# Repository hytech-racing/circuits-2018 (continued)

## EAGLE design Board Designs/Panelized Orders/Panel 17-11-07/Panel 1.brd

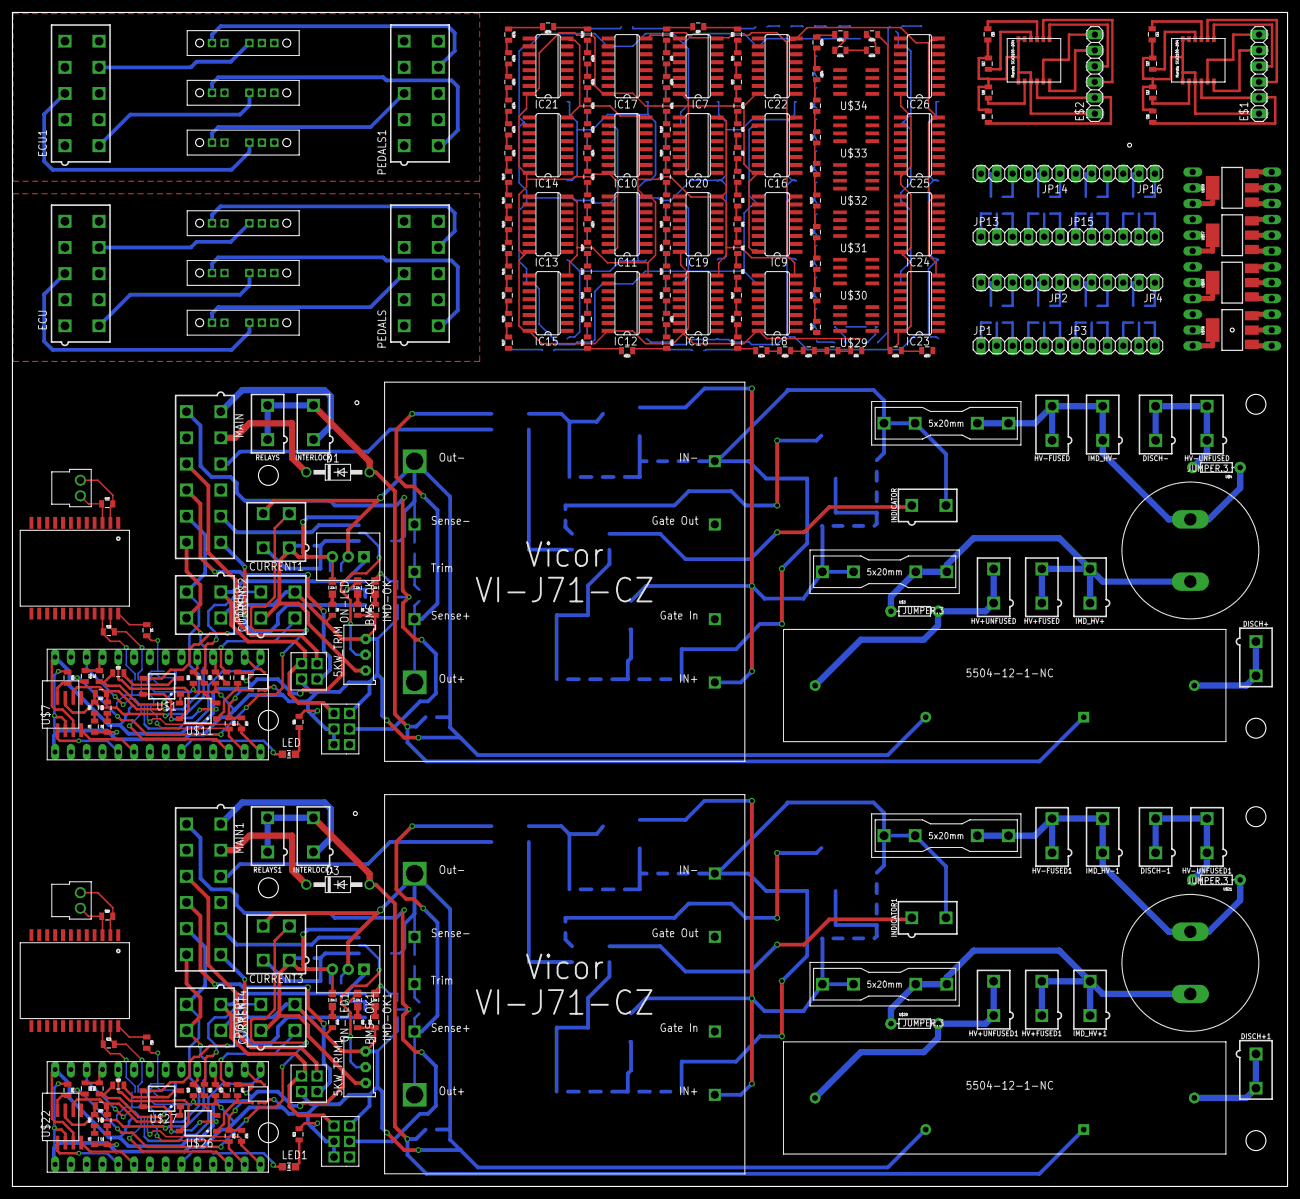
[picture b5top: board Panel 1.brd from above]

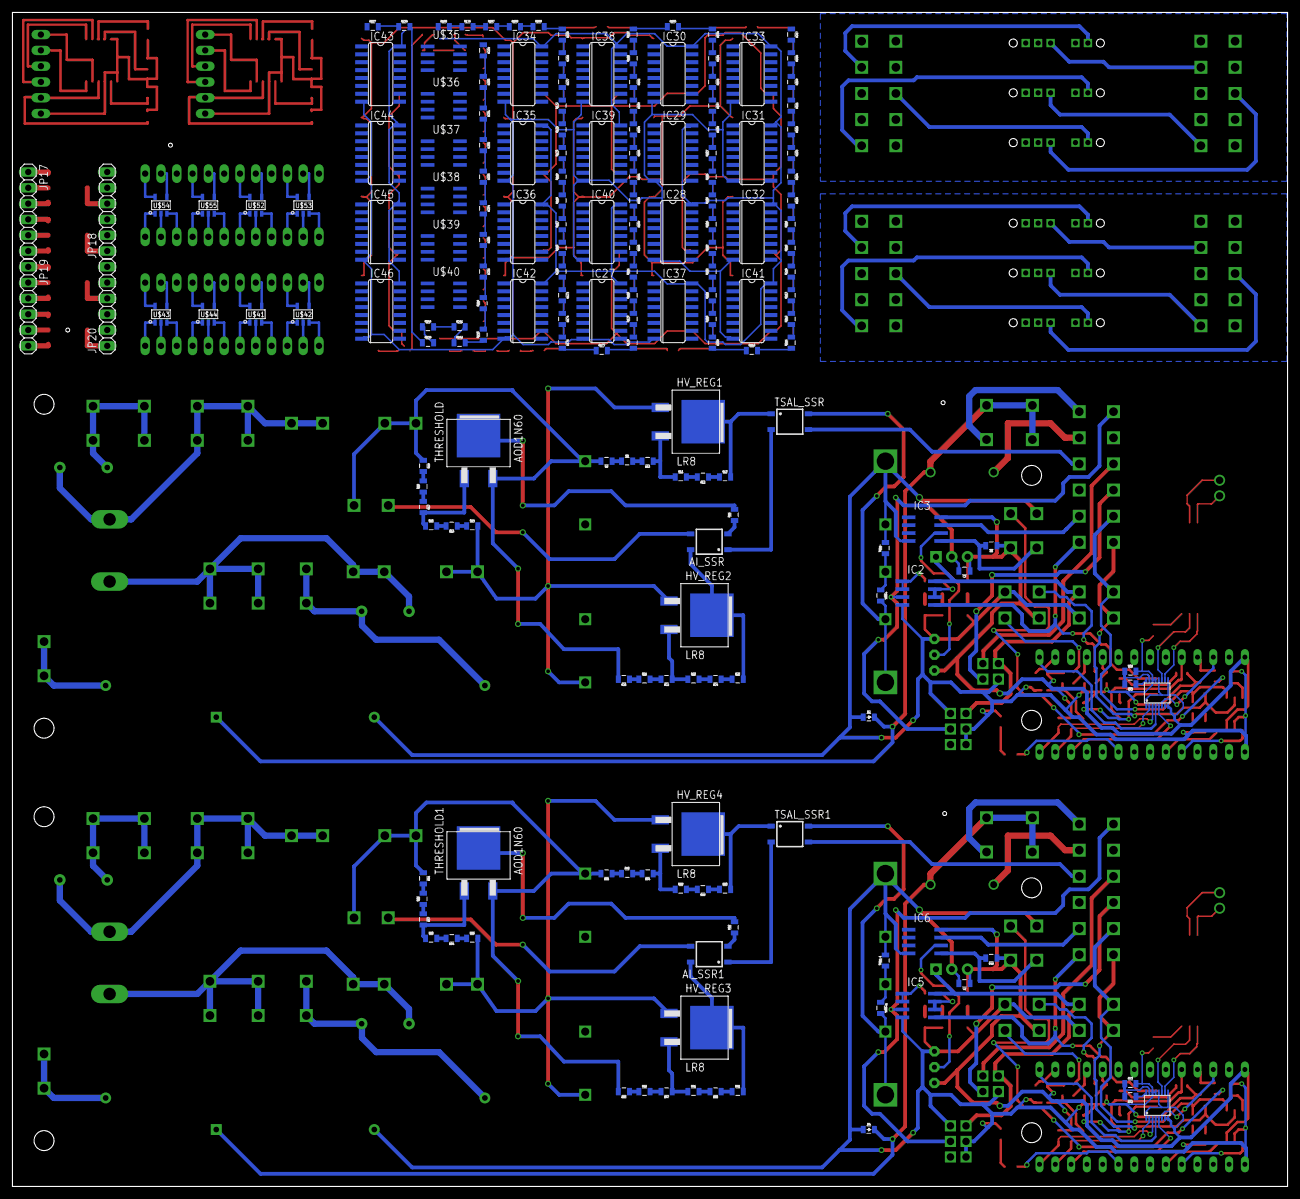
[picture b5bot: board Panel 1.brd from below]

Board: 2 copper layers, 205.0 x 188.7 mm, 448 parts (186 on the bottom side), 404 nets.

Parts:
5KW_TRIM, 5KW_TRIM1: TRIMPOT_3296
AI_SSR, AI_SSR1: CPC1002N; SOP04
BMS-OK, BMS-OK1: LED-805
C1, C5: 220uF; LLS2V221MELZ
C2, C3: 1uF; 0805
C4, C10: 27pF; 0805
C6, C7, C8, C9: 560pF; 0805
C11, C12, C13, C14, C15, C16, C17, C18: 130 nF; 0805
CURRENT1, CURRENT2, CURRENT3, CURRENT4: MINIFIT_5566-4
D1, D3: DIODE; DO-41
D2, D4: DIODE0805; 0805_D
DISCH+, DISCH+1: DISCHARGE+; MINIFIT_5566-2
DISCH-, DISCH-1: DISCHARGE -; MINIFIT_5566-2
E$1, E$2: 1X06
ECU, ECU1: MINIFIT_5566-10
EM, EM1: CONNECTOR-4; NANO-FIT_VERTICAL-4
FUSE, FUSE1, FUSE2, FUSE3: 1A; 0751.0110
HV+FUSED, HV+FUSED1: MINIFIT_5566-2
HV+UNFUSED, HV+UNFUSED1: FSAE; MINIFIT_5566-2
HV-FUSED, HV-FUSED1: MINIFIT_5566-2
HV-UNFUSED, HV-UNFUSED1: FSAE; MINIFIT_5566-2
HV_REG1, HV_REG2, HV_REG3, HV_REG4: LR8; TO-252
IC1, IC4: TO-220
IC2, IC3, IC5, IC6: NE5532SOIC; SOIC-08
IC7, IC8, IC9, IC10, IC11, IC12, IC13, IC14, IC15, IC16, IC17, IC18, IC19, IC20, IC21, IC22, IC23, IC24, IC25, IC26, IC27, IC28, IC29, IC30, IC31, IC32, IC33, IC34, IC35, IC36, IC37, IC38, IC39, IC40, IC41, IC42, IC43, IC44, IC45, IC46: 74LS258D; SO16
IMD, IMD1: CONNECTOR-6; NANO-FIT_VERTICAL-6
IMD-OK, IMD-OK1: LED-805
IMD_HV+, IMD_HV+1: MINIFIT_5566-2
IMD_HV-, IMD_HV-1: MINIFIT_5566-2
INDICATOR, INDICATOR1: MINIFIT_5566-2
INTERLOCK, INTERLOCK1: MINIFIT_5566-2
ISOSPI, ISOSPI1: CONNECTOR-2; NANO-FIT_VERTICAL-2
JP1, JP2, JP3, JP4, JP13, JP14, JP15, JP16, JP17, JP18, JP19, JP20: 1X06
LED, LED1: LED-805
MAIN, MAIN1: MINIFIT_5566-12
ON-LED, ON-LED1: LED-805
PEDALS, PEDALS1: MINIFIT_5566-10
POWER, POWER1: MINIFIT_5566-4
R1, R2, R26, R30, R33, R34, R44, R52, R70, R72, R73, R78, R79, R82: 1k; 0805
R3, R4, R31, R45, R46, R71, R85, R86, R87, R88, R89, R90, R91, R92, R93, R94, R95, R96, R97, R98, R99, R100, R101, R102, R103, R104, R105, R106, R107, R108, R109, R110, R111, R112, R113, R114, R115, R116, R117, R118, R119, R120, R121, R122, R123, R124, R125, R126, R127, R128, R129, R130, R131, R132, R133, R134, R135, R136, R137, R138, R139, R140, R141, R142, R143, R144, R145, R146, R147, R148, R149, R150, R151, R152, R153, R154, R155, R156, R157, R158, R159, R160, R161, R162, R163, R164, R165, R166, R167, R168, R169, R170, R171, R172, R173, R174, R175, R176, R177, R178, R179, R180, R181, R182, R183, R184, R185, R186, R187, R188, R189, R190, R191, R192, R193, R194, R195, R196, R197, R198, R199, R200, R201, R202, R203, R204, R205, R206, R207, R208, R209, R210, R211, R212, R213, R214, R215, R216, R217, R218, R219, R220, R221, R222, R223, R224, R225, R226, R227, R228, R229, R230, R231, R232, R233, R234, R235, R236, R237, R238, R239, R240, R241, R242, R243, R244: 0805
R5, R28, R29, R40, R49, R68, R69, R84: 100; 0805
R6, R48: 10k; 0805
R7, R11, R12, R13, R23, R24, R25, R32, R36, R37, R41, R42, R43, R53, R58, R59, R60, R61, R75, R76, R80, R81: 2k; 0805
R8, R9, R10, R64, R65, R66: 8.2k; 0805
R14, R15, R16, R50, R54, R55: 500k; 0805
R17, R18, R19, R51, R56, R57: 40k; 0805
R20, R21, R22, R47, R62, R63: 20k; 0805
R27, R35, R67, R74: 120; 0805
R38, R77: 68; 0805
R39, R83: 200; 0805
RELAYS, RELAYS1: MINIFIT_5566-2
THRESHOLD, THRESHOLD1: AOD1N60; TO-252
TRIM+, TRIM+1: 0805
TRIM-, TRIM-1: 0805
TSAL_SSR, TSAL_SSR1: CPC1002N; SOP04
U$1, U$11, U$26, U$27: SOP04
U$2, U$28: SM51589PEL
U$3, U$4, U$20, U$21: JUMPER.3; AXIAL-0.3
U$5, U$19: HV_DCDC_VI-J71-CZ
U$6, U$13, U$14, U$15, U$16, U$17: SS-14D0839-VG5PA
U$7, U$22, U$29, U$30, U$31, U$32, U$33, U$34, U$35, U$36, U$37, U$38, U$39, U$40: MCP2551; SOIC-08
U$8, U$23: LTC6820; MSOP-16
U$9, U$24: TEENSY_3.2_SIMPLE
U$10, U$25: STWD100; SOT23-5
U$12, U$18: 5504-12-1-NC
U$41, U$43, U$52, U$54: SN74LVC1G06; SOT-23-5
U$42, U$44, U$53, U$55: SN74LVC1G07; SOT-23-5
U$45, U$56: SCA3100-D04
U$57, U$58, U$59, U$60: SOT223

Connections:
5KW_TRIG: 5KW_TRIM.2, IC3.6
5KW_TRIG1: 5KW_TRIM1.2, IC6.6
+3V1: U$23.6, U$24.3.3V
+3V3: U$8.6, U$9.3.3V
+5V: 5KW_TRIM.1, C3.1, CURRENT1.1, CURRENT2.1, IC1.3, IC3.8, ON-LED.A, R6.1, R36.1, R37.1, R38.1, U$1.4, U$7.3, U$8.1, U$8.7, U$8.8, U$8.9, U$8.12, U$9.VIN, U$10.VCC
+5V1: ECU.1, ECU.4, ECU.7, PEDALS.1, PEDALS.4, PEDALS.7, U$6.4, U$13.4, U$14.4
+5V3: 5KW_TRIM1.1, C2.1, CURRENT3.1, CURRENT4.1, IC4.3, IC6.8, ON-LED1.A, R48.1, R75.1, R76.1, R77.1, U$22.3, U$23.1, U$23.7, U$23.8, U$23.9, U$23.12, U$24.VIN, U$25.VCC, U$27.4
+5V4: ECU1.1, ECU1.4, ECU1.7, PEDALS1.1, PEDALS1.4, PEDALS1.7, U$15.4, U$16.4, U$17.4
+12V: EM.P$1, IC1.1, IC2.8, IMD.P$1, POWER.1
+12V1: EM1.P$1, IC4.1, IC5.8, IMD1.P$1, POWER1.1
BMS_OK: IC2.5, MAIN.6, U$1.3
BMS_OK1: IC5.5, MAIN1.6, U$27.3
BMS_WATCH: U$1.1, U$11.3
BMS_WATCH1: U$26.3, U$27.1
BSPD_CUR_FAULT: IC3.7, MAIN.5
BSPD_CUR_FAULT1: IC6.7, MAIN1.5
CANH: MAIN.12, POWER.4, R27.2, R28.2, U$7.7
CANH1: MAIN1.12, POWER1.4, R67.2, R68.2, U$22.7
CANL: MAIN.11, POWER.3, R27.1, R29.2, U$7.6
CANL1: MAIN1.11, POWER1.3, R67.1, R69.2, U$22.6
CS: U$8.5, U$9.D10(TX2)
CS1: U$23.5, U$24.D10(TX2)
CUR_SENSE_1: CURRENT1.2, IC3.5, R6.2
CUR_SENSE_2: R1.1, R32.2, U$9.A3
CUR_SENSE_3: CURRENT3.2, IC6.5, R48.2
CUR_SENSE_4: R78.1, R80.2, U$24.A3
DISCHARGE1: HV+UNFUSED.1, HV+UNFUSED.2, U$3.P$2, U$12.CONTACT1
DISCHARGE2: DISCH+.1, DISCH+.2, U$12.CONTACT2
DISCHARGE3: DISCH-.1, DISCH-.2, HV-UNFUSED.1, HV-UNFUSED.2, U$4.P$2
DISCHARGE4: DISCH+1.1, DISCH+1.2, U$18.CONTACT2
DISCHARGE5: HV+UNFUSED1.1, HV+UNFUSED1.2, U$18.CONTACT1, U$20.P$2
DISCHARGE6: DISCH-1.1, DISCH-1.2, HV-UNFUSED1.1, HV-UNFUSED1.2, U$21.P$2
EM_IO1: EM.P$3, MAIN.9
EM_IO2: EM.P$4, MAIN.10
EM_IO3: EM1.P$3, MAIN1.9
EM_IO4: EM1.P$4, MAIN1.10
GND: 5KW_TRIM.3, C3.2, C4.2, C8.1, C9.1, CURRENT1.4, CURRENT2.4, D2.A, EM.P$2, IC1.2, IC2.4, IC3.4, IMD.P$2, IMD.P$3, IMD.P$4, POWER.2, R3.1, R4.2, R5.2, R7.1, R30.1, R31.2, R32.1, R34.2, R39.1, R43.1, TRIM-.2, U$5.8SENSE-, U$5.9VOUT-, U$7.2, U$8.13, U$8.14, U$9.GND, U$10.EN, U$10.GND, U$11.2, U$12.COIL-
GND1: ECU.2, ECU.5, ECU.8, PEDALS.2, PEDALS.5, PEDALS.8, U$6.3, U$13.3, U$14.3
GND2: ECU1.2, ECU1.5, ECU1.8, PEDALS1.2, PEDALS1.5, PEDALS1.8, U$15.3, U$16.3, U$17.3
GND3: 5KW_TRIM1.3, C2.2, C6.1, C7.1, C10.2, CURRENT3.4, CURRENT4.4, D4.A, EM1.P$2, IC4.2, IC5.4, IC6.4, IMD1.P$2, IMD1.P$3, IMD1.P$4, POWER1.2, R42.1, R45.1, R46.2, R49.2, R70.1, R71.2, R73.2, R80.1, R81.1, R83.1, TRIM-1.2, U$18.COIL-, U$19.8SENSE-, U$19.9VOUT-, U$22.2, U$23.13, U$23.14, U$24.GND, U$25.EN, U$25.GND, U$26.2
GND4: IC7.8, IC8.8, IC9.8, IC10.8, IC11.8, IC12.8, IC13.8, IC14.8, IC15.8, IC16.8, IC17.8, IC18.8, IC19.8, IC20.8, IC21.8, IC22.8, IC23.8, IC24.8, IC25.8, IC26.8
GND5: IC27.8, IC28.8, IC29.8, IC30.8, IC31.8, IC32.8, IC33.8, IC34.8, IC35.8, IC36.8, IC37.8, IC38.8, IC39.8, IC40.8, IC41.8, IC42.8, IC43.8, IC44.8, IC45.8, IC46.8
GND6: C11.2, C12.2, C13.2, C14.2, U$45.AVSS, U$45.DVSS, U$45.EMC_GND, U$45.RESERVED
GND7: C15.2, C16.2, C17.2, C18.2, U$56.AVSS, U$56.DVSS, U$56.EMC_GND, U$56.RESERVED
HV+FUSED: C1.P$1, FUSE.L1, FUSE.L2, HV+FUSED.1, HV+FUSED.2, IMD_HV+.1, IMD_HV+.2, U$3.P$1
HV+FUSED1: C5.P$1, FUSE2.L1, FUSE2.L2, HV+FUSED1.1, HV+FUSED1.2, IMD_HV+1.1, IMD_HV+1.2, U$20.P$1
HV+FUSED_1A: FUSE.R1, FUSE.R2, HV_REG1.1, HV_REG2.1, R14.2, U$5.1VIN+
HV+FUSED_1A1: FUSE2.R1, FUSE2.R2, HV_REG3.1, HV_REG4.1, R55.2, U$19.1VIN+
HV-FUSED: C1.P$2, FUSE1.L1, FUSE1.L2, HV-FUSED.1, HV-FUSED.2, IMD_HV-.1, IMD_HV-.2, U$4.P$1
HV-FUSED1: C5.P$2, FUSE3.L1, FUSE3.L2, HV-FUSED1.1, HV-FUSED1.2, IMD_HV-1.1, IMD_HV-1.2, U$21.P$1
HV-FUSED_1A: FUSE1.R1, FUSE1.R2, INDICATOR.2, R8.2, R19.1, R20.2, THRESHOLD.3, U$5.4VIN-
HV-FUSED_1A1: FUSE3.R1, FUSE3.R2, INDICATOR1.2, R51.1, R63.2, R66.2, THRESHOLD1.3, U$19.4VIN-
ISOSPI-M: ISOSPI.P$2, R40.1, U$2.3
ISOSPI-M1: ISOSPI1.P$2, R84.1, U$28.3
ISOSPI-P: ISOSPI.P$1, R40.2, U$2.2
ISOSPI-P1: ISOSPI1.P$1, R84.2, U$28.2
MISO: R37.2, U$8.3, U$9.D12
MISO1: R76.2, U$23.3, U$24.D12
MOSI: R36.2, U$8.2, U$9.D11
MOSI1: R75.2, U$23.2, U$24.D11
unnamed: AI_SSR.4, HV_REG2.2(TAB), R25.2
unnamed: HV_REG1.2(TAB), R13.2, TSAL_SSR.1
unnamed: ON-LED.C, R5.1
unnamed: R39.2, U$1.2
unnamed: AI_SSR.2, R26.1
unnamed: AI_SSR.1, TSAL_SSR.2
unnamed: AI_SSR.3, INDICATOR.1
unnamed: R8.1, R9.1
unnamed: R26.2, THRESHOLD.2(TAB)
unnamed: R14.1, R15.1
unnamed: R15.2, R16.2
unnamed: R17.1, R18.1
unnamed: R18.2, R19.2
unnamed: R9.2, R10.2
unnamed: HV_REG2.3, R22.1, R23.1
unnamed: R11.2, R12.2
unnamed: R12.1, R13.1
unnamed: HV_REG1.3, R10.1, R11.1
unnamed: R23.2, R24.2
unnamed: R24.1, R25.1
unnamed: R21.2, R22.2
unnamed: R16.1, R17.2, THRESHOLD.1
unnamed: R20.1, R21.1
unnamed: ECU.9, U$6.COM
unnamed: U$7.1, U$9.D3(CANTX)
unnamed: R30.2, U$7.8
unnamed: C8.2, R28.1
unnamed: C9.2, R29.1
unnamed: LED.C, R31.1
unnamed: CURRENT2.2, R1.2
unnamed: R33.1, U$8.16
unnamed: R33.2, R34.1, U$8.15
unnamed: R35.1, U$2.22, U$8.10
unnamed: R35.2, U$2.23, U$8.11
unnamed: C4.1, U$2.24
unnamed: U$7.4, U$9.D4(CANRX)
unnamed: LED.A, U$9.D7(RX3)
unnamed: R38.2, U$10.WDO, U$11.1
unnamed: ECU.6, U$13.COM
unnamed: U$9.A8, U$11.4
unnamed: ECU.3, U$14.COM
unnamed: IC2.1, IC2.2, IMD-OK.A
unnamed: BMS-OK.A, IC2.6, IC2.7
unnamed: BMS-OK.C, R4.1
unnamed: IMD-OK.C, R3.2
unnamed: PEDALS.9, U$6.1
unnamed: PEDALS.6, U$13.1
unnamed: PEDALS.3, U$14.1
unnamed: ECU1.9, U$15.COM
unnamed: U$9.A0, U$10.WDI
unnamed: ECU1.6, U$16.COM
unnamed: ECU1.3, U$17.COM
unnamed: CURRENT1.3, R44.2
unnamed: CURRENT2.3, R2.2
unnamed: PEDALS1.9, U$15.1
unnamed: PEDALS1.6, U$16.1
unnamed: PEDALS1.3, U$17.1
unnamed: AI_SSR1.4, HV_REG3.2(TAB), R61.2
unnamed: HV_REG3.3, R41.1, R47.1
unnamed: IC5.1, IC5.2, IMD-OK1.A
unnamed: BMS-OK1.A, IC5.6, IC5.7
unnamed: BMS-OK1.C, R46.1
unnamed: IMD-OK1.C, R45.2
unnamed: ON-LED1.C, R49.1
unnamed: HV_REG4.2(TAB), R53.2, TSAL_SSR1.1
unnamed: R54.1, R55.1
unnamed: R50.2, R54.2
unnamed: R56.1, R57.1
unnamed: R51.2, R56.2
unnamed: AI_SSR1.2, R52.1
unnamed: AI_SSR1.1, TSAL_SSR1.2
unnamed: AI_SSR1.3, INDICATOR1.1
unnamed: HV_REG4.3, R59.1, R64.1
unnamed: R64.2, R65.2
unnamed: R65.1, R66.1
unnamed: R50.1, R57.2, THRESHOLD1.1
unnamed: R58.2, R59.2
unnamed: R53.1, R58.1
unnamed: R52.2, THRESHOLD1.2(TAB)
unnamed: R41.2, R60.2
unnamed: R60.1, R61.1
unnamed: R47.2, R62.2
unnamed: R62.1, R63.1
unnamed: U$22.1, U$24.D3(CANTX)
unnamed: R70.2, U$22.8
unnamed: C6.2, R68.1
unnamed: C7.2, R69.1
unnamed: LED1.C, R71.1
unnamed: R72.1, U$23.16
unnamed: R72.2, R73.1, U$23.15
unnamed: R74.1, U$23.10, U$28.22
unnamed: R74.2, U$23.11, U$28.23
unnamed: C10.1, U$28.24
unnamed: U$22.4, U$24.D4(CANRX)
unnamed: LED1.A, U$24.D7(RX3)
unnamed: R77.2, U$25.WDO, U$26.1
unnamed: U$24.A8, U$26.4
unnamed: U$24.A0, U$25.WDI
unnamed: CURRENT4.2, R78.2
unnamed: CURRENT4.3, R79.2
unnamed: CURRENT3.3, R82.2
unnamed: R83.2, U$27.2
unnamed: R85.2, R96.1
unnamed: R96.2, R107.1
unnamed: R107.2, R118.1
unnamed: R129.2, R140.1
unnamed: R140.2, R146.1
unnamed: R146.2, R147.1
unnamed: R118.2, R129.1
unnamed: R86.1, R148.2
unnamed: R86.2, R87.1
unnamed: R87.2, R88.1
unnamed: R89.2, R90.1
unnamed: R90.2, R91.1
unnamed: R91.2, R92.1
unnamed: R88.2, R89.1
unnamed: R92.2, R147.2
unnamed: R93.2, R94.1
unnamed: R94.2, R95.1
unnamed: R95.2, R97.1
unnamed: R98.2, R99.1
unnamed: R99.2, R100.1
unnamed: R100.2, R101.1
unnamed: R97.2, R98.1
unnamed: R102.2, R103.1
unnamed: R103.2, R104.1
unnamed: R104.2, R105.1
unnamed: R106.2, R108.1
unnamed: R108.2, R109.1
unnamed: R109.2, R110.1
unnamed: R105.2, R106.1
unnamed: R101.2, R110.2
unnamed: R93.1, R148.1
unnamed: R111.2, R112.1
unnamed: R112.2, R113.1
unnamed: R113.2, R114.1
unnamed: R115.2, R116.1
unnamed: R116.2, R117.1
unnamed: R117.2, R119.1
unnamed: R114.2, R115.1
unnamed: R120.2, R121.1
unnamed: R121.2, R122.1
unnamed: R122.2, R123.1
unnamed: R124.2, R125.1
unnamed: R125.2, R126.1
unnamed: R126.2, R127.1
unnamed: R123.2, R124.1
unnamed: R119.2, R127.2
unnamed: R128.2, R130.1
unnamed: R130.2, R131.1
unnamed: R131.2, R132.1
unnamed: R133.2, R134.1
unnamed: R134.2, R135.1
unnamed: R135.2, R136.1
unnamed: R132.2, R133.1
unnamed: R137.2, R138.1
unnamed: R138.2, R139.1
unnamed: R139.2, R141.1
unnamed: R142.2, R143.1
unnamed: R143.2, R144.1
unnamed: R144.2, R145.1
unnamed: R141.2, R142.1
unnamed: R136.2, R145.2
unnamed: R120.1, R128.1
unnamed: R102.1, R111.1
unnamed: R149.2, R150.1
unnamed: R150.2, R151.1
unnamed: R151.2, R152.1
unnamed: R153.2, R154.1
unnamed: R154.2, R155.1
unnamed: R155.2, R156.1
unnamed: R152.2, R153.1
unnamed: R157.2, R158.1
unnamed: R158.2, R159.1
unnamed: R159.2, R160.1
unnamed: R161.2, R162.1
unnamed: R162.2, R163.1
unnamed: R163.2, R164.1
unnamed: R160.2, R161.1
unnamed: R156.2, R164.2
unnamed: R165.2, R176.1
unnamed: R176.2, R187.1
unnamed: R187.2, R198.1
unnamed: R209.2, R220.1
unnamed: R220.2, R226.1
unnamed: R226.2, R227.1
unnamed: R198.2, R209.1
unnamed: R166.1, R228.2
unnamed: R166.2, R167.1
unnamed: R167.2, R168.1
unnamed: R169.2, R170.1
unnamed: R170.2, R171.1
unnamed: R171.2, R172.1
unnamed: R168.2, R169.1
unnamed: R172.2, R227.2
unnamed: R173.2, R174.1
unnamed: R174.2, R175.1
unnamed: R175.2, R177.1
unnamed: R178.2, R179.1
unnamed: R179.2, R180.1
unnamed: R180.2, R181.1
unnamed: R177.2, R178.1
unnamed: R182.2, R183.1
unnamed: R183.2, R184.1
unnamed: R184.2, R185.1
unnamed: R186.2, R188.1
unnamed: R188.2, R189.1
unnamed: R189.2, R190.1
unnamed: R185.2, R186.1
unnamed: R181.2, R190.2
unnamed: R173.1, R228.1
unnamed: R191.2, R192.1
unnamed: R192.2, R193.1
unnamed: R193.2, R194.1
unnamed: R195.2, R196.1
unnamed: R196.2, R197.1
unnamed: R197.2, R199.1
unnamed: R194.2, R195.1
unnamed: R200.2, R201.1
unnamed: R201.2, R202.1
unnamed: R202.2, R203.1
unnamed: R204.2, R205.1
unnamed: R205.2, R206.1
unnamed: R206.2, R207.1
unnamed: R203.2, R204.1
unnamed: R199.2, R207.2
unnamed: R208.2, R210.1
unnamed: R210.2, R211.1
unnamed: R211.2, R212.1
unnamed: R213.2, R214.1
unnamed: R214.2, R215.1
unnamed: R215.2, R216.1
unnamed: R212.2, R213.1
unnamed: R217.2, R218.1
unnamed: R218.2, R219.1
unnamed: R219.2, R221.1
unnamed: R222.2, R223.1
unnamed: R223.2, R224.1
unnamed: R224.2, R225.1
unnamed: R221.2, R222.1
unnamed: R216.2, R225.2
unnamed: R200.1, R208.1
unnamed: R182.1, R191.1
unnamed: R229.2, R230.1
unnamed: R230.2, R231.1
unnamed: R231.2, R232.1
unnamed: R233.2, R234.1
unnamed: R234.2, R235.1
unnamed: R235.2, R236.1
unnamed: R232.2, R233.1
unnamed: R237.2, R238.1
unnamed: R238.2, R239.1
unnamed: R239.2, R240.1
unnamed: R241.2, R242.1
unnamed: R242.2, R243.1
unnamed: R243.2, R244.1
unnamed: R240.2, R241.1
unnamed: R236.2, R244.2
unnamed: JP2.1, U$41.5
unnamed: JP2.2, U$41.4
unnamed: JP2.4, U$42.5
unnamed: JP2.5, U$42.4
unnamed: JP1.6, U$41.1
unnamed: JP1.5, U$41.2
unnamed: JP1.4, U$41.3
unnamed: JP1.3, U$42.1
unnamed: JP1.2, U$42.2
unnamed: JP1.1, U$42.3
unnamed: JP4.1, U$43.5
unnamed: JP4.2, U$43.4
unnamed: JP4.4, U$44.5
unnamed: JP4.5, U$44.4
unnamed: JP3.6, U$43.1
unnamed: JP3.5, U$43.2
unnamed: JP3.4, U$43.3
unnamed: JP3.3, U$44.1
unnamed: JP3.2, U$44.2
unnamed: JP3.1, U$44.3
unnamed: C12.1, U$45.A_EXTC
unnamed: C13.1, U$45.D_EXTC
unnamed: C14.1, U$45.DVIO
unnamed: JP14.1, U$52.5
unnamed: JP14.2, U$52.4
unnamed: JP14.4, U$53.5
unnamed: JP14.5, U$53.4
unnamed: JP13.6, U$52.1
unnamed: JP13.5, U$52.2
unnamed: JP13.4, U$52.3
unnamed: JP13.3, U$53.1
unnamed: JP13.2, U$53.2
unnamed: JP13.1, U$53.3
unnamed: JP16.1, U$54.5
unnamed: JP16.2, U$54.4
unnamed: JP16.4, U$55.5
unnamed: JP16.5, U$55.4
unnamed: JP15.6, U$54.1
unnamed: JP15.5, U$54.2
unnamed: JP15.4, U$54.3
unnamed: JP15.3, U$55.1
unnamed: JP15.2, U$55.2
unnamed: JP15.1, U$55.3
unnamed: C16.1, U$56.A_EXTC
unnamed: C17.1, U$56.D_EXTC
unnamed: C18.1, U$56.DVIO
unnamed: JP18.1, U$57.4
unnamed: JP17.6, U$57.1
unnamed: JP17.5, U$57.2
unnamed: JP17.4, U$57.3
unnamed: JP17.3, U$59.1
unnamed: JP17.2, U$59.2
unnamed: JP17.1, U$59.3
unnamed: JP18.4, U$59.4
unnamed: JP20.1, U$58.4
unnamed: JP20.4, U$60.4
unnamed: JP19.6, U$58.1
unnamed: JP19.5, U$58.2
unnamed: JP19.4, U$58.3
unnamed: JP19.3, U$60.1
unnamed: JP19.2, U$60.2
unnamed: JP19.1, U$60.3
OKHS: IC2.3, IMD.P$5, MAIN.7
OKHS1: IC5.3, IMD1.P$5, MAIN1.7
SCK: U$8.4, U$9.D13
SCK1: U$23.4, U$24.D13
SHUTDOWN1: D3.A, D4.C, INTERLOCK1.2, RELAYS1.1, RELAYS1.2, U$18.COIL+
SHUTDOWN2: INTERLOCK1.1, MAIN1.1
SHUTDOWN6: INTERLOCK.1, MAIN.1
SHUTDOWN7: D1.A, D2.C, INTERLOCK.2, RELAYS.1, RELAYS.2, U$12.COIL+
SHUTDOWN7_EXT_OUT: D1.C, MAIN.2
SHUTDOWN7_EXT_OUT1: D3.C, MAIN1.2
TEMP_SENSE_1: R7.2, R44.1, U$9.A9
TEMP_SENSE_2: R2.1, R43.2, U$9.A2
TEMP_SENSE_3: R79.1, R81.2, U$24.A2
TEMP_SENSE_4: R42.2, R82.1, U$24.A9
TRIM: TRIM+.1, TRIM-.1, U$5.7TRIM
TRIM1: TRIM+1.1, TRIM-1.1, U$19.7TRIM
TSAL+: MAIN.3, TSAL_SSR.3
TSAL+1: MAIN1.3, TSAL_SSR1.3
TSAL_1: TRIM+.2, TSAL_SSR.4, U$5.5VOUT+, U$5.6SENSE+
TSAL_2: TRIM+1.2, TSAL_SSR1.4, U$19.5VOUT+, U$19.6SENSE+
VCC: IC7.16, IC8.16, IC9.16, IC10.16, IC11.16, IC12.16, IC13.16, IC14.16, IC15.16, IC16.16, IC17.16, IC18.16, IC19.16, IC20.16, IC21.16, IC22.16, IC23.16, IC24.16, IC25.16, IC26.16
VCC1: IC27.16, IC28.16, IC29.16, IC30.16, IC31.16, IC32.16, IC33.16, IC34.16, IC35.16, IC36.16, IC37.16, IC38.16, IC39.16, IC40.16, IC41.16, IC42.16, IC43.16, IC44.16, IC45.16, IC46.16
VDD: C11.1, U$45.VDD
VDD1: C15.1, U$56.VDD
